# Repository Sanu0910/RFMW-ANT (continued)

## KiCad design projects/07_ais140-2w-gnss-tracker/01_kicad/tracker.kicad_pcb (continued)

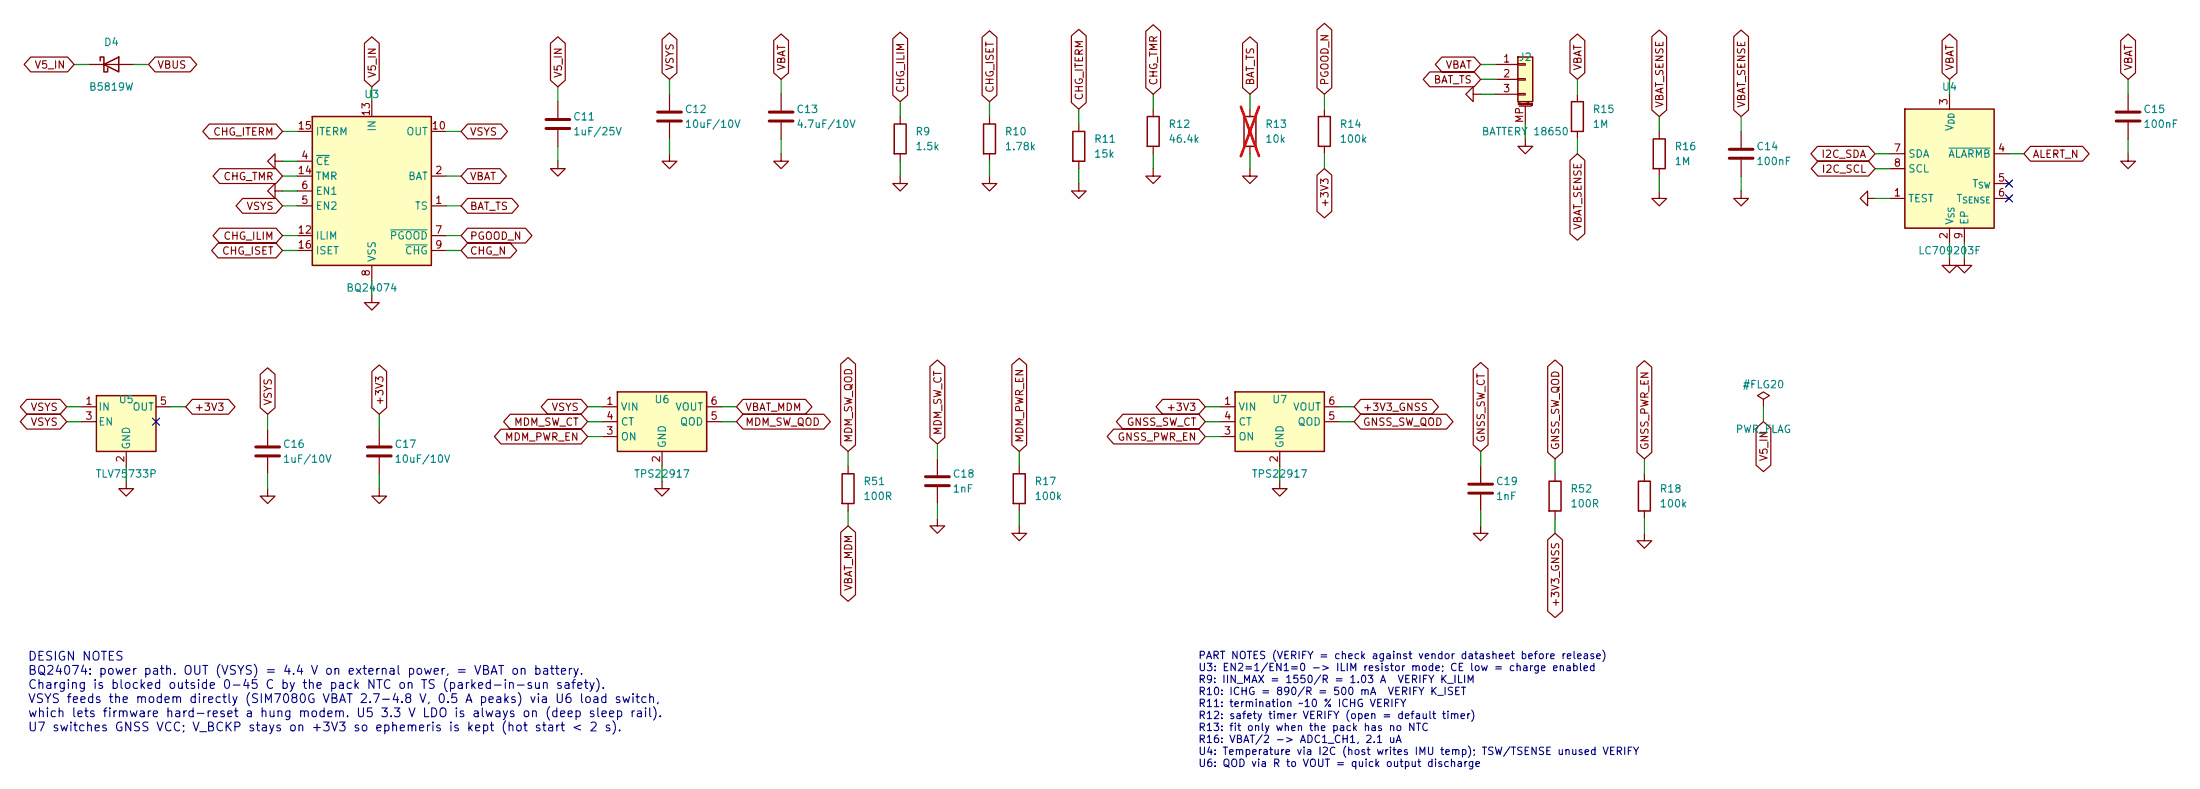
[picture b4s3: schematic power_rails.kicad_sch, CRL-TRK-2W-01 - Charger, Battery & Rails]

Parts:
C11: 1uF/25V; C_0603_1608Metric; MPN 0603 MLCC X7R/X5R, AEC-Q200
C12, C17: 10uF/10V; C_0805_2012Metric; MPN 0805 MLCC X7R/X5R, AEC-Q200
C13: 4.7uF/10V; C_0805_2012Metric; MPN 0805 MLCC X7R/X5R, AEC-Q200
C14, C15: 100nF; C_0402_1005Metric; MPN 0402 MLCC X7R/X5R, AEC-Q200
C16: 1uF/10V; C_0603_1608Metric; MPN 0603 MLCC X7R/X5R, AEC-Q200
C18, C19: 1nF; C_0402_1005Metric; MPN 0402 MLCC X7R/X5R, AEC-Q200
D4: B5819W; D_SOD-123; MPN B5819W
J2: BATTERY 18650; JST_PH_S3B-PH-SM4-TB_1x03-1MP_P2.00mm_Horizontal; MPN S3B-PH-SM4-TB(LF)(SN)
R9: 1.5k; R_0402_1005Metric; MPN 0402 1% thick film, AEC-Q200
R10: 1.78k; R_0402_1005Metric; MPN 0402 1% thick film, AEC-Q200
R11: 15k; R_0402_1005Metric; MPN 0402 1% thick film, AEC-Q200
R12: 46.4k; R_0402_1005Metric; MPN 0402 1% thick film, AEC-Q200
R13: 10k; R_0402_1005Metric; MPN 0402 1% thick film, AEC-Q200; not fitted
R14, R17, R18: 100k; R_0402_1005Metric; MPN 0402 1% thick film, AEC-Q200
R15, R16: 1M; R_0402_1005Metric; MPN 0402 1% thick film, AEC-Q200
R51, R52: 100R; R_0402_1005Metric; MPN 0402 1% thick film, AEC-Q200
U3: BQ24074; VQFN-16-1EP_3x3mm_P0.5mm_EP1.6x1.6mm; MPN BQ24074RGTR
U4: LC709203F; WDFN-8-1EP_4x3mm_P0.65mm_EP2.4x1.8mm; MPN LC709203FQH-01TWG
U5: TLV75733P; SOT-23-5; MPN TLV75733PDBVR
U6, U7: TPS22917; SOT-23-6; MPN TPS22917DBVR

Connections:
+3V3: C17.1, R14.2, U5.5 (OUT), U7.1 (VIN); also elsewhere on the board
+3V3_GNSS: R52.2, U7.6 (VOUT); also elsewhere on the board
ALERT_N: U4.4 (~ALARMB); also elsewhere on the board
BAT_TS: J2.2, R13.1, U3.1 (TS)
CHG_ILIM: R9.1, U3.12 (ILIM)
CHG_ISET: R10.1, U3.16 (ISET)
CHG_ITERM: R11.1, U3.15 (ITERM)
CHG_N: U3.9 (~CHG); also elsewhere on the board
GND: C11.2, C12.2, C13.2, C14.2, C15.2, C16.2, C17.2, C18.2, C19.2, J2.3, J2.MP (MountPin), R9.2, R10.2, R11.2, R12.2, R13.2, R16.2, R17.2, R18.2, U3.4 (~CE), U3.6 (EN1), U3.8 (VSS), U3.17 (VSS), U4.1 (TEST), U4.2 (V_{SS}), U4.9 (EP), U5.2 (GND), U6.2 (GND), U7.2 (GND); also elsewhere on the board
GNSS_PWR_EN: R18.1, U7.3 (ON); also elsewhere on the board
GNSS_SW_CT: C19.1, U7.4 (CT)
GNSS_SW_QOD: R52.1, U7.5 (QOD)
I2C_SCL: U4.8 (SCL); also elsewhere on the board
I2C_SDA: U4.7 (SDA); also elsewhere on the board
MDM_PWR_EN: R17.1, U6.3 (ON); also elsewhere on the board
MDM_SW_CT: C18.1, U6.4 (CT)
MDM_SW_QOD: R51.1, U6.5 (QOD)
unnamed: R12.1, U3.14 (TMR)
PGOOD_N: R14.1, U3.7 (~PGOOD); also elsewhere on the board
V5_IN: C11.1, D4.1 (K), U3.13 (IN); also elsewhere on the board
VBAT: C13.1, C15.1, J2.1, R15.1, U3.2 (BAT), U3.3 (BAT), U4.3 (V_{DD}); also elsewhere on the board
VBAT_MDM: R51.2, U6.6 (VOUT); also elsewhere on the board
VBAT_SENSE: C14.1, R15.2, R16.1; also elsewhere on the board
VBUS: D4.2 (A); also elsewhere on the board
VSYS: C12.1, C16.1, U3.5 (EN2), U3.10 (OUT), U3.11 (OUT), U5.1 (IN), U5.3 (EN), U6.1 (VIN); also elsewhere on the board

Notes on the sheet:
DESIGN NOTES BQ24074: power path. OUT (VSYS) = 4.4 V on external power, = VBAT on battery. Charging is blocked outside 0-45 C by the pack NTC on TS (parked-in-sun safety). VSYS feeds the modem directly (SIM7080G VBAT 2.7-4.8 V, 0.5 A peaks) via U6 load switch, which lets firmware hard-reset a hung 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
PART NOTES (VERIFY = check against vendor datasheet before release) U3: EN2=1/EN1=0 -> ILIM resistor mode; CE low = charge enabled R9: IIN_MAX = 1550/R = 1.03 A VERIFY K_ILIM R10: ICHG = 890/R = 500 mA VERIFY K_ISET R11: termination ~10 % ICHG VERIFY R12: safety timer VERIFY (open = default timer) 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

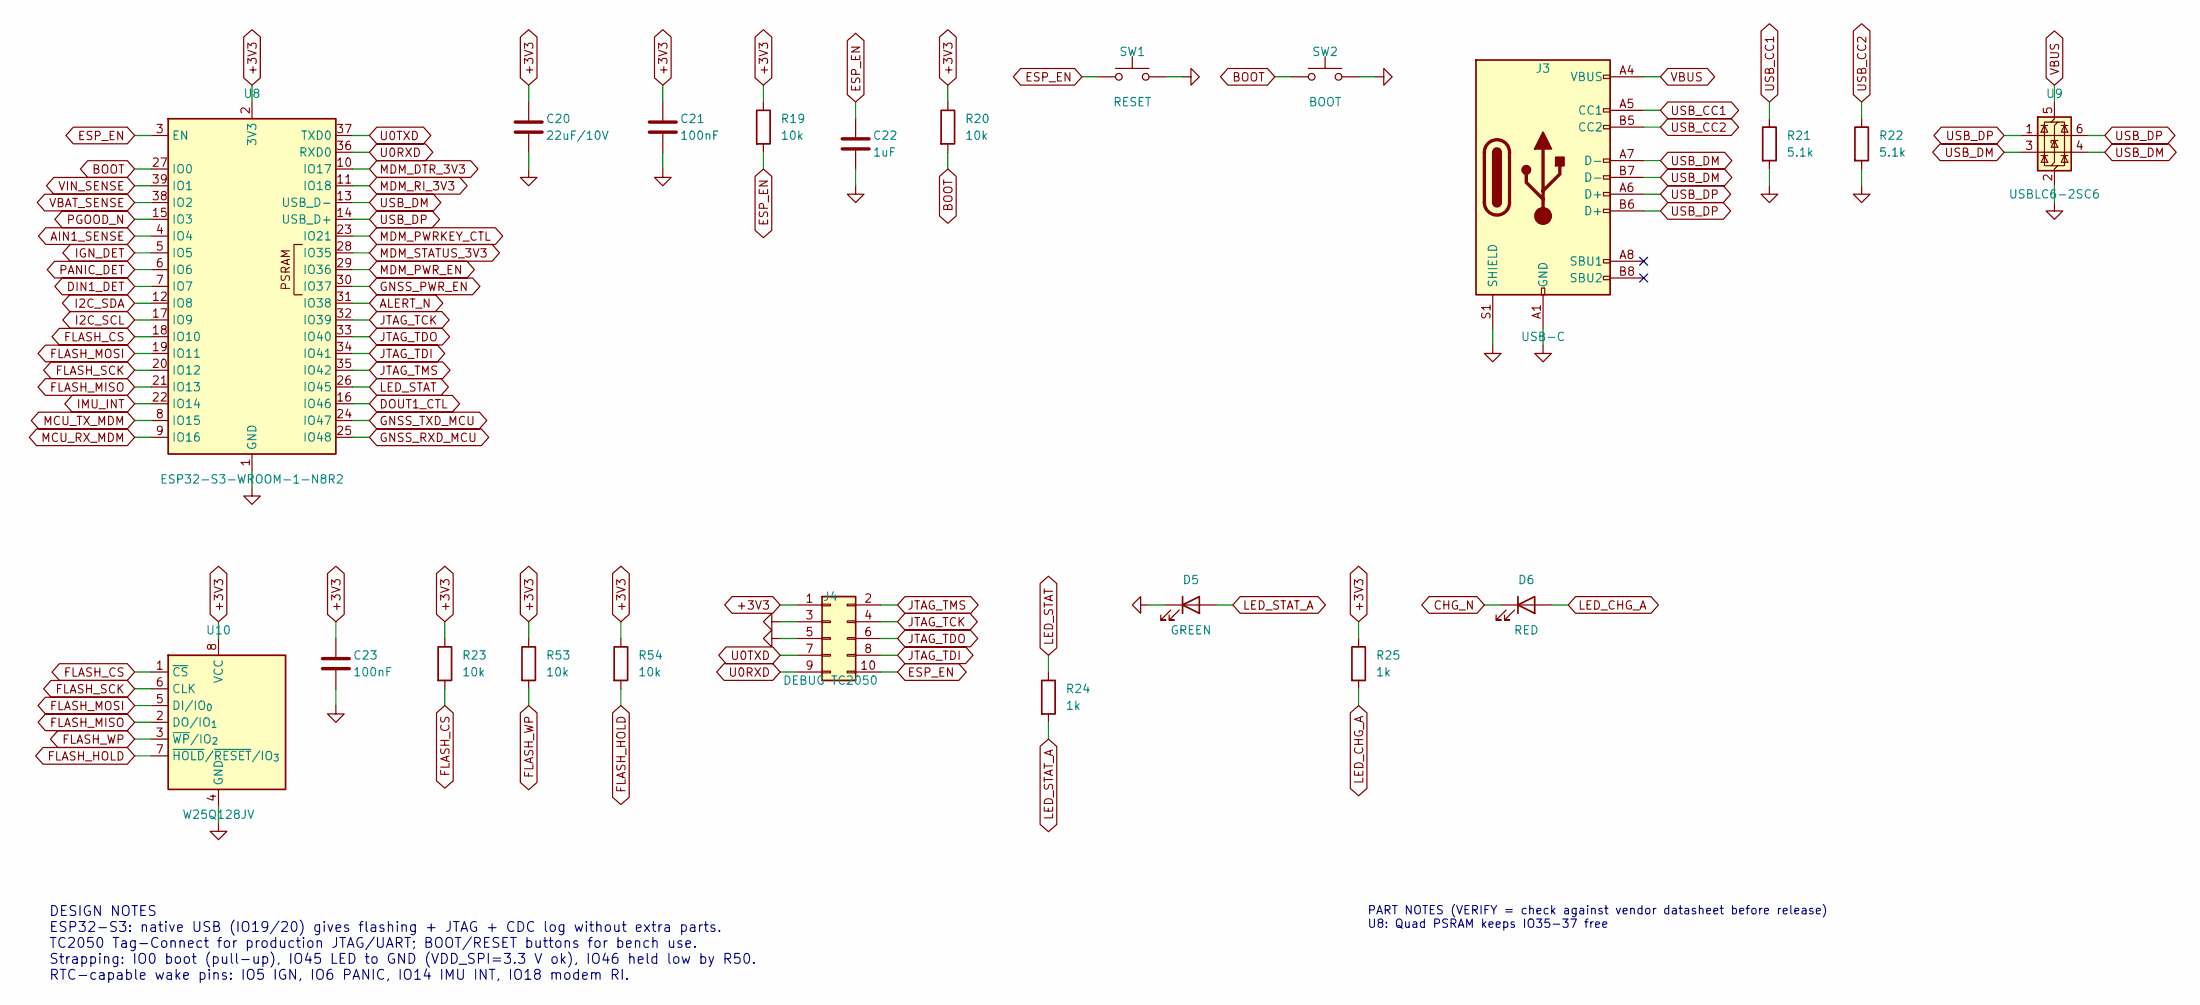
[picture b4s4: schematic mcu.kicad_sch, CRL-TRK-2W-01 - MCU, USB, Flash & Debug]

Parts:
C20: 22uF/10V; C_0805_2012Metric; MPN 0805 MLCC X7R/X5R, AEC-Q200
C21, C23: 100nF; C_0402_1005Metric; MPN 0402 MLCC X7R/X5R, AEC-Q200
C22: 1uF; C_0603_1608Metric; MPN 0603 MLCC X7R/X5R, AEC-Q200
D5: GREEN; LED_0603_1608Metric; MPN LTST-C191KGKT
D6: RED; LED_0603_1608Metric; MPN LTST-C191KRKT
J3: USB-C; USB_C_Receptacle_HRO_TYPE-C-31-M-12; MPN TYPE-C-31-M-12
J4: DEBUG TC2050; Tag-Connect_TC2050-IDC-NL_2x05_P1.27mm_Vertical; MPN Tag-Connect TC2050-IDC-NL (footprint on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
R19, R20, R23, R53, R54: 10k; R_0402_1005Metric; MPN 0402 1% thick film, AEC-Q200
R21, R22: 5.1k; R_0402_1005Metric; MPN 0402 1% thick film, AEC-Q200
R24, R25: 1k; R_0402_1005Metric; MPN 0402 1% thick film, AEC-Q200
SW1: RESET; SW_Push_1P1T_XKB_TS-1187A; MPN TS-1187A-B-A-B
SW2: BOOT; SW_Push_1P1T_XKB_TS-1187A; MPN TS-1187A-B-A-B
U8: ESP32-S3-WROOM-1-N8R2; ESP32-S3-WROOM-1_EdgeAntenna; MPN ESP32-S3-WROOM-1-N8R2
U9: USBLC6-2SC6; SOT-23-6; MPN USBLC6-2SC6
U10: W25Q128JV; SOIC-8_5.3x5.3mm_P1.27mm; MPN W25Q128JVSIQ

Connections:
+3V3: C20.1, C21.1, C23.1, J4.1, R19.1, R20.1, R23.1, R25.1, R53.1, R54.1, U8.2 (3V3), U10.8 (VCC); also elsewhere on the board
AIN1_SENSE: U8.4 (IO4); also elsewhere on the board
ALERT_N: U8.31 (IO38); also elsewhere on the board
BOOT: R20.2, SW2.1, U8.27 (IO0); also elsewhere on the board
CHG_N: D6.1 (K); also elsewhere on the board
DIN1_DET: U8.7 (IO7); also elsewhere on the board
DOUT1_CTL: U8.16 (IO46); also elsewhere on the board
ESP_EN: C22.1, J4.10, R19.2, SW1.1, U8.3 (EN); also elsewhere on the board
FLASH_CS: R23.2, U8.18 (IO10), U10.1 (~CS)
FLASH_HOLD: R54.2, U10.7 (~HOLD/~RESET/IO_{3})
FLASH_MISO: U8.21 (IO13), U10.2 (DO/IO_{1})
FLASH_MOSI: U8.19 (IO11), U10.5 (DI/IO_{0})
FLASH_SCK: U8.20 (IO12), U10.6 (CLK)
FLASH_WP: R53.2, U10.3 (~WP/IO_{2})
GND: C20.2, C21.2, C22.2, C23.2, D5.1 (K), J3.A1 (GND), J3.A12 (GND), J3.B1 (GND), J3.B12 (GND), J3.S1 (SHIELD), J4.3, J4.5, R21.2, R22.2, SW1.2, SW2.2, U8.1 (GND), U8.40 (GND), U8.41 (GND), U9.2 (GND), U10.4 (GND); also elsewhere on the board
GNSS_PWR_EN: U8.30 (IO37); also elsewhere on the board
GNSS_RXD_MCU: U8.25 (IO48); also elsewhere on the board
GNSS_TXD_MCU: U8.24 (IO47); also elsewhere on the board
I2C_SCL: U8.17 (IO9); also elsewhere on the board
I2C_SDA: U8.12 (IO8); also elsewhere on the board
IGN_DET: U8.5 (IO5); also elsewhere on the board
IMU_INT: U8.22 (IO14); also elsewhere on the board
JTAG_TCK: J4.4, U8.32 (IO39); also elsewhere on the board
JTAG_TDI: J4.8, U8.34 (IO41); also elsewhere on the board
JTAG_TDO: J4.6, U8.33 (IO40); also elsewhere on the board
JTAG_TMS: J4.2, U8.35 (IO42); also elsewhere on the board
LED_CHG_A: D6.2 (A), R25.2
LED_STAT: R24.1, U8.26 (IO45)
LED_STAT_A: D5.2 (A), R24.2
MCU_RX_MDM: U8.9 (IO16); also elsewhere on the board
MCU_TX_MDM: U8.8 (IO15); also elsewhere on the board
MDM_DTR_3V3: U8.10 (IO17); also elsewhere on the board
MDM_PWRKEY_CTL: U8.23 (IO21); also elsewhere on the board
MDM_PWR_EN: U8.29 (IO36); also elsewhere on the board
MDM_RI_3V3: U8.11 (IO18); also elsewhere on the board
MDM_STATUS_3V3: U8.28 (IO35); also elsewhere on the board
PANIC_DET: U8.6 (IO6); also elsewhere on the board
PGOOD_N: U8.15 (IO3); also elsewhere on the board
U0RXD: J4.9, U8.36 (RXD0); also elsewhere on the board
U0TXD: J4.7, U8.37 (TXD0); also elsewhere on the board
USB_CC1: J3.A5 (CC1), R21.1
USB_CC2: J3.B5 (CC2), R22.1
USB_DM: J3.A7 (D-), J3.B7 (D-), U8.13 (USB_D-), U9.3 (I/O2), U9.4 (I/O2)
USB_DP: J3.A6 (D+), J3.B6 (D+), U8.14 (USB_D+), U9.1 (I/O1), U9.6 (I/O1)
VBAT_SENSE: U8.38 (IO2); also elsewhere on the board
VBUS: J3.A4 (VBUS), J3.A9 (VBUS), J3.B4 (VBUS), J3.B9 (VBUS), U9.5 (VBUS); also elsewhere on the board
VIN_SENSE: U8.39 (IO1); also elsewhere on the board

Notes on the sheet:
DESIGN NOTES ESP32-S3: native USB (IO19/20) gives flashing + JTAG + CDC log without extra parts. TC2050 Tag-Connect for production JTAG/UART; BOOT/RESET buttons for bench use. Strapping: IO0 boot (pull-up), IO45 LED to GND (VDD_SPI=3.3 V ok), IO46 held low by R50. RTC-capable wake pins: IO5 IGN, IO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
PART NOTES (VERIFY = check against vendor datasheet before release) U8: Quad PSRAM keeps IO35-37 free

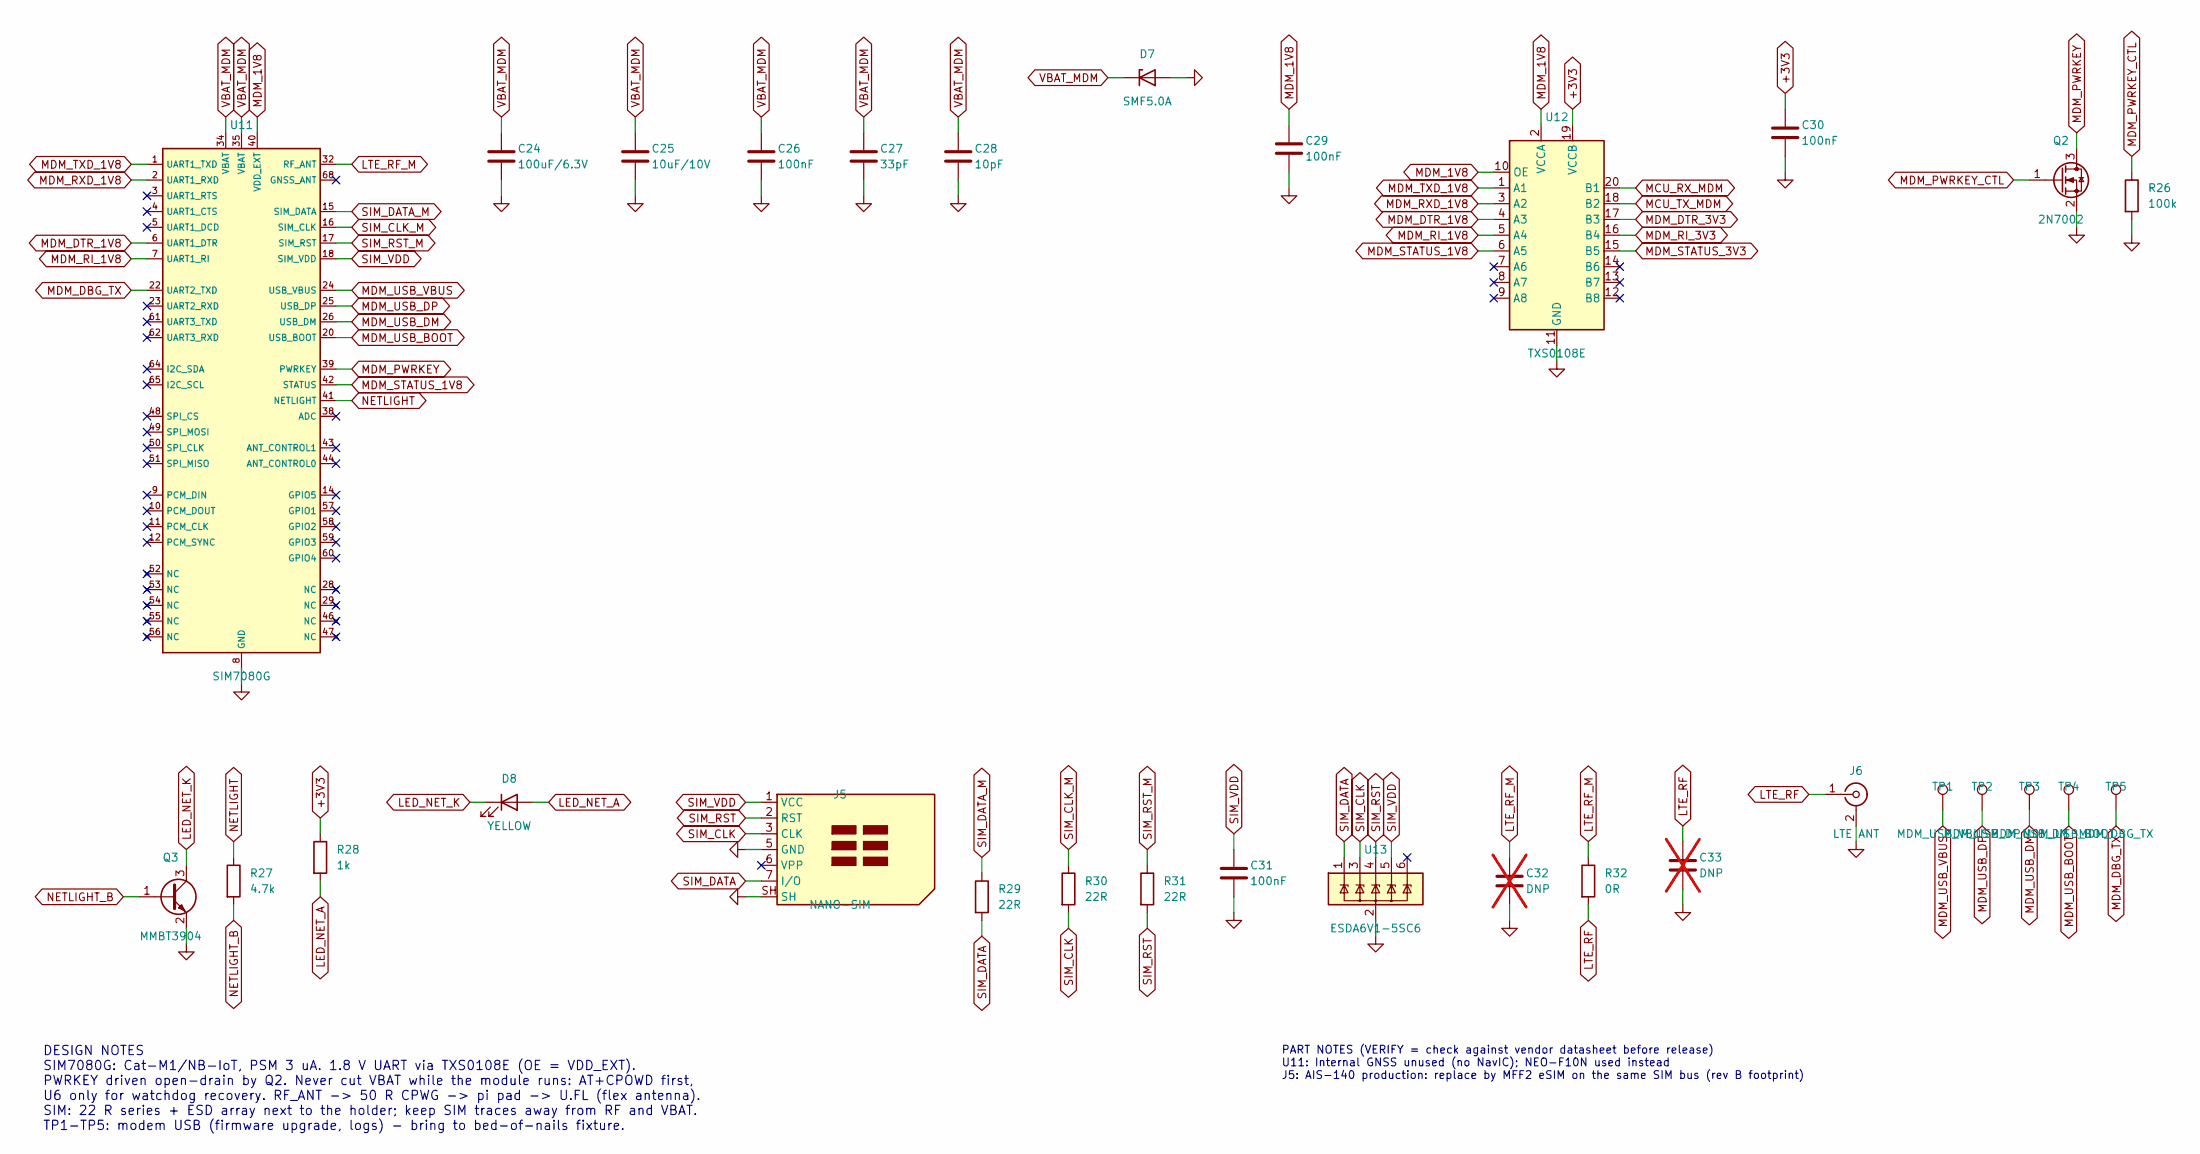
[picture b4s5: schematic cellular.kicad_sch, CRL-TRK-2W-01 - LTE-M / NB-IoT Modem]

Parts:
C24: 100uF/6.3V; C_1210_3225Metric; MPN 1210 MLCC X7R/X5R, AEC-Q200
C25: 10uF/10V; C_0805_2012Metric; MPN 0805 MLCC X7R/X5R, AEC-Q200
C26, C29, C30, C31: 100nF; C_0402_1005Metric; MPN 0402 MLCC X7R/X5R, AEC-Q200
C27: 33pF; C_0402_1005Metric; MPN 0402 C0G 50V
C28: 10pF; C_0402_1005Metric; MPN 0402 C0G 50V
C32, C33: DNP; C_0402_1005Metric; MPN 0402 C0G (tune); not fitted
D7: SMF5.0A; D_SOD-123F; MPN SMF5.0A
D8: YELLOW; LED_0603_1608Metric; MPN LTST-C191KSKT
J5: NANO-SIM; nanoSIM_GCT_SIM8060-6-0-14-00; MPN SIM8060-6-0-14-00-A
J6: LTE ANT; U.FL_Hirose_U.FL-R-SMT-1_Vertical; MPN U.FL-R-SMT-1(10)
Q2: 2N7002; SOT-23; MPN 2N7002K-7
Q3: MMBT3904; SOT-23; MPN MMBT3904
R26: 100k; R_0402_1005Metric; MPN 0402 1% thick film, AEC-Q200
R27: 4.7k; R_0402_1005Metric; MPN 0402 1% thick film, AEC-Q200
R28: 1k; R_0402_1005Metric; MPN 0402 1% thick film, AEC-Q200
R29, R30, R31: 22R; R_0402_1005Metric; MPN 0402 1% thick film, AEC-Q200
R32: 0R; R_0402_1005Metric; MPN 0402 0R jumper
TP1: MDM_USB_VBUS; TestPoint_Pad_D1.0mm; MPN Test pad 1.0 mm (no part)
TP2: MDM_USB_DP; TestPoint_Pad_D1.0mm; MPN Test pad 1.0 mm (no part)
TP3: MDM_USB_DM; TestPoint_Pad_D1.0mm; MPN Test pad 1.0 mm (no part)
TP4: MDM_USB_BOOT; TestPoint_Pad_D1.0mm; MPN Test pad 1.0 mm (no part)
TP5: MDM_DBG_TX; TestPoint_Pad_D1.0mm; MPN Test pad 1.0 mm (no part)
U11: SIM7080G; SIMCom_SIM7080G_LCC-77; MPN SIM7080G
U12: TXS0108E; TSSOP-20_4.4x6.5mm_P0.65mm; MPN TXS0108EPWR
U13: ESDA6V1-5SC6; SOT-23-6; MPN ESDA6V1-5SC6

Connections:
+3V3: C30.1, R28.1, U12.19 (VCCB); also elsewhere on the board
GND: C24.2, C25.2, C26.2, C27.2, C28.2, C29.2, C30.2, C31.2, C32.2, C33.2, D7.2 (A), J5.5 (GND), J5.SH, J6.2 (Ext), Q2.2 (S), Q3.2 (E), R26.2, U11.8 (GND), U11.13 (GND), U11.19 (GND), U11.21 (GND), U11.27 (GND), U11.30 (GND), U11.31 (GND), U11.33 (GND), U11.36 (GND), U11.37 (GND), U11.45 (GND), U11.63 (GND), U11.66 (GND), U11.67 (GND), U11.69 (GND), U11.70 (GND), U11.71 (GND), U11.72 (GND), U11.73 (GND), U11.74 (GND), U11.75 (GND), U11.76 (GND), U11.77 (GND), U12.11 (GND), U13.2 (GND); also elsewhere on the board
LED_NET_A: D8.2 (A), R28.2
LED_NET_K: D8.1 (K), Q3.3 (C)
LTE_RF: C33.1, J6.1 (In), R32.2
LTE_RF_M: C32.1, R32.1, U11.32 (RF_ANT)
MCU_RX_MDM: U12.20 (B1); also elsewhere on the board
MCU_TX_MDM: U12.18 (B2); also elsewhere on the board
MDM_1V8: C29.1, U11.40 (VDD_EXT), U12.2 (VCCA), U12.10 (OE)
MDM_DBG_TX: TP5.1, U11.22 (UART2_TXD)
MDM_DTR_1V8: U11.6 (UART1_DTR), U12.4 (A3)
MDM_DTR_3V3: U12.17 (B3); also elsewhere on the board
MDM_PWRKEY: Q2.3 (D), U11.39 (PWRKEY)
MDM_PWRKEY_CTL: Q2.1 (G), R26.1; also elsewhere on the board
MDM_RI_1V8: U11.7 (UART1_RI), U12.5 (A4)
MDM_RI_3V3: U12.16 (B4); also elsewhere on the board
MDM_RXD_1V8: U11.2 (UART1_RXD), U12.3 (A2)
MDM_STATUS_1V8: U11.42 (STATUS), U12.6 (A5)
MDM_STATUS_3V3: U12.15 (B5); also elsewhere on the board
MDM_TXD_1V8: U11.1 (UART1_TXD), U12.1 (A1)
MDM_USB_BOOT: TP4.1, U11.20 (USB_BOOT)
MDM_USB_DM: TP3.1, U11.26 (USB_DM)
MDM_USB_DP: TP2.1, U11.25 (USB_DP)
MDM_USB_VBUS: TP1.1, U11.24 (USB_VBUS)
NETLIGHT: R27.1, U11.41 (NETLIGHT)
NETLIGHT_B: Q3.1 (B), R27.2
SIM_CLK: J5.3 (CLK), R30.2, U13.3 (IO2)
SIM_CLK_M: R30.1, U11.16 (SIM_CLK)
SIM_DATA: J5.7 (I/O), R29.2, U13.1 (IO1)
SIM_DATA_M: R29.1, U11.15 (SIM_DATA)
SIM_RST: J5.2 (RST), R31.2, U13.4 (IO3)
SIM_RST_M: R31.1, U11.17 (SIM_RST)
SIM_VDD: C31.1, J5.1 (VCC), U11.18 (SIM_VDD), U13.5 (IO4)
VBAT_MDM: C24.1, C25.1, C26.1, C27.1, C28.1, D7.1 (K), U11.34 (VBAT), U11.35 (VBAT); also elsewhere on the board

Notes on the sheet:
DESIGN NOTES SIM7080G: Cat-M1/NB-IoT, PSM 3 uA. 1.8 V UART via TXS0108E (OE = VDD_EXT). PWRKEY driven open-drain by Q2. Never cut VBAT while the module runs: AT+CPOWD first, U6 only for watchdog recovery. RF_ANT -> 50 R CPWG -> pi pad -> U.FL (flex antenna). SIM: 22 R series + ESD array next to the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
PART NOTES (VERIFY = check against vendor datasheet before release) U11: Internal GNSS unused (no NavIC); NEO-F10N used instead J5: AIS-140 production: replace by MFF2 eSIM on the same SIM bus (rev B footprint)

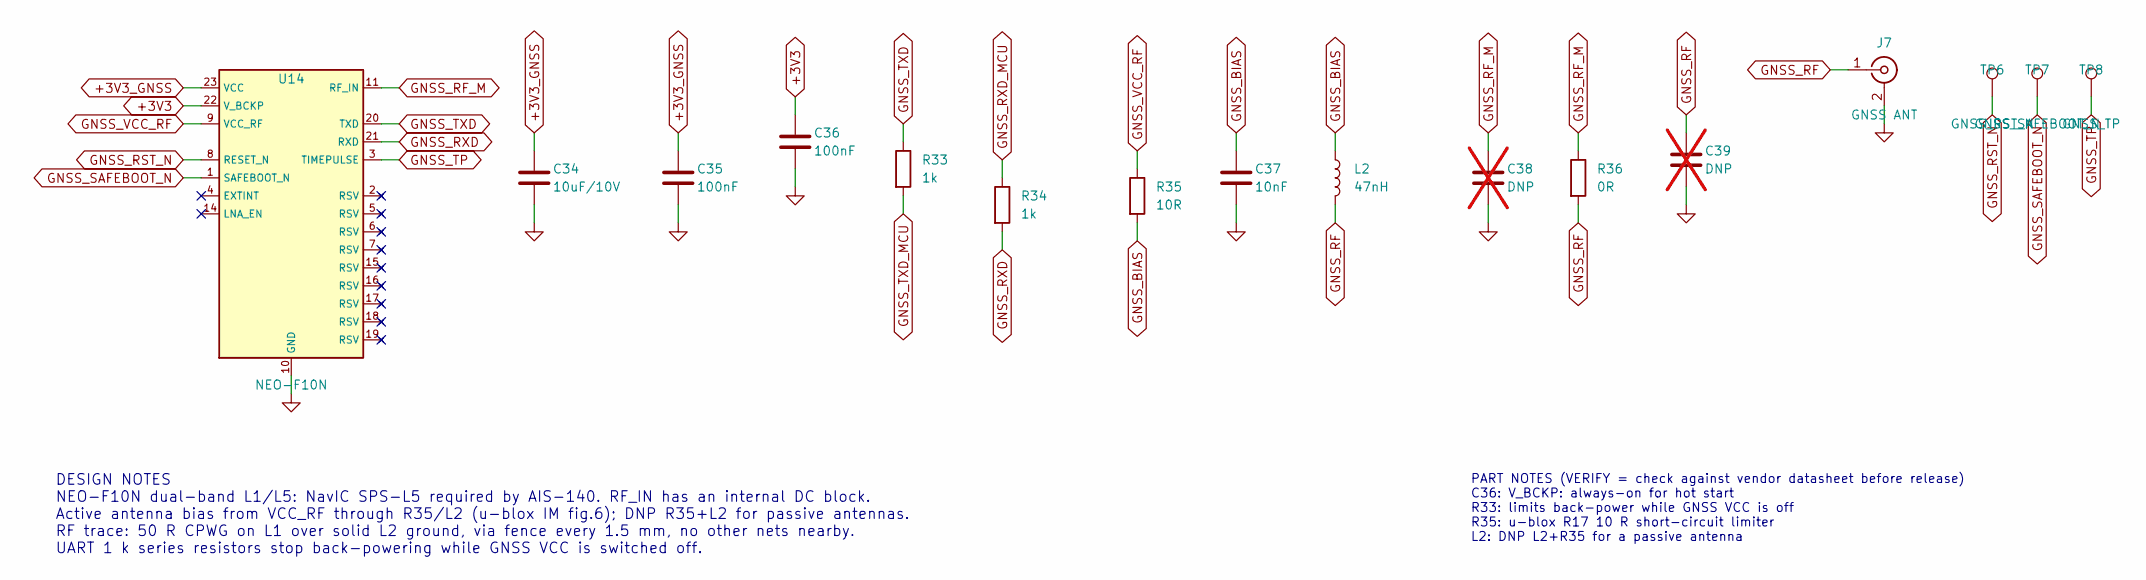
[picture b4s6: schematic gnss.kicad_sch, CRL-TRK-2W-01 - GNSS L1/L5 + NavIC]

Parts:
C34: 10uF/10V; C_0805_2012Metric; MPN 0805 MLCC X7R/X5R, AEC-Q200
C35, C36: 100nF; C_0402_1005Metric; MPN 0402 MLCC X7R/X5R, AEC-Q200
C37: 10nF; C_0402_1005Metric; MPN 0402 MLCC X7R/X5R, AEC-Q200
C38, C39: DNP; C_0402_1005Metric; MPN 0402 C0G (tune); not fitted
J7: GNSS ANT; U.FL_Hirose_U.FL-R-SMT-1_Vertical; MPN U.FL-R-SMT-1(10)
L2: 47nH; L_0402_1005Metric; MPN LQG15HS47NJ02D
R33, R34: 1k; R_0402_1005Metric; MPN 0402 1% thick film, AEC-Q200
R35: 10R; R_0402_1005Metric; MPN 0402 1% thick film, AEC-Q200
R36: 0R; R_0402_1005Metric; MPN 0402 0R jumper
TP6: GNSS_RST_N; TestPoint_Pad_D1.0mm; MPN Test pad 1.0 mm (no part)
TP7: GNSS_SAFEBOOT_N; TestPoint_Pad_D1.0mm; MPN Test pad 1.0 mm (no part)
TP8: GNSS_TP; TestPoint_Pad_D1.0mm; MPN Test pad 1.0 mm (no part)
U14: NEO-F10N; ublox_NEO; MPN NEO-F10N-00B

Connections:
+3V3: C36.1, U14.22 (V_BCKP); also elsewhere on the board
+3V3_GNSS: C34.1, C35.1, U14.23 (VCC); also elsewhere on the board
GND: C34.2, C35.2, C36.2, C37.2, C38.2, C39.2, J7.2 (Ext), U14.10 (GND), U14.12 (GND), U14.13 (GND), U14.24 (GND); also elsewhere on the board
GNSS_BIAS: C37.1, L2.1, R35.2
GNSS_RF: C39.1, J7.1 (In), L2.2, R36.2
GNSS_RF_M: C38.1, R36.1, U14.11 (RF_IN)
GNSS_RST_N: TP6.1, U14.8 (RESET_N)
GNSS_RXD: R34.2, U14.21 (RXD)
GNSS_RXD_MCU: R34.1; also elsewhere on the board
GNSS_SAFEBOOT_N: TP7.1, U14.1 (SAFEBOOT_N)
GNSS_TP: TP8.1, U14.3 (TIMEPULSE)
GNSS_TXD: R33.1, U14.20 (TXD)
GNSS_TXD_MCU: R33.2; also elsewhere on the board
GNSS_VCC_RF: R35.1, U14.9 (VCC_RF)

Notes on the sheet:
DESIGN NOTES NEO-F10N dual-band L1/L5: NavIC SPS-L5 required by AIS-140. RF_IN has an internal DC block. Active antenna bias from VCC_RF through R35/L2 (u-blox IM fig.6); DNP R35+L2 for passive antennas. RF trace: 50 R CPWG on L1 over solid L2 ground, via fence every 1.5 mm, no other nets nearby. U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
PART NOTES (VERIFY = check against vendor datasheet before release) C36: V_BCKP: always-on for hot start R33: limits back-power while GNSS VCC is off R35: u-blox R17 10 R short-circuit limiter L2: DNP L2+R35 for a passive antenna

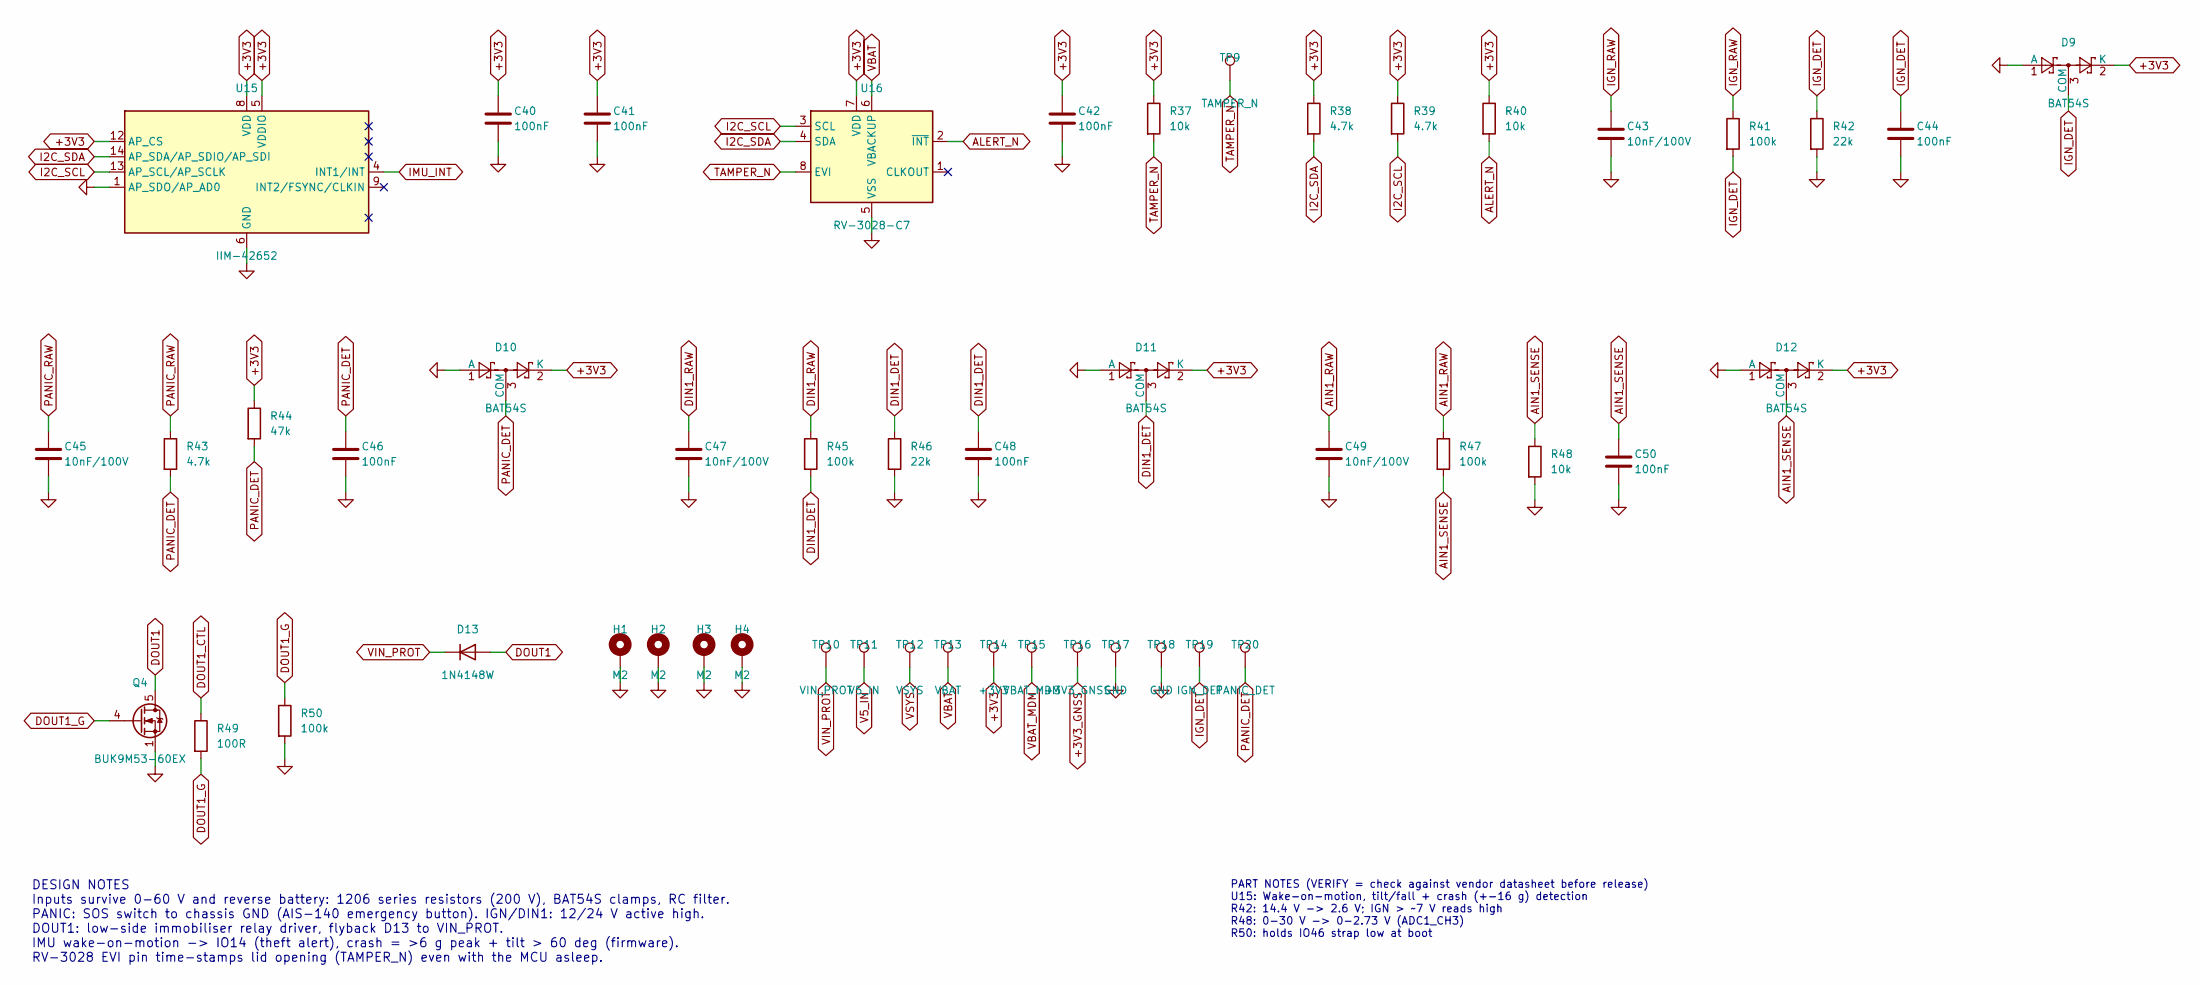
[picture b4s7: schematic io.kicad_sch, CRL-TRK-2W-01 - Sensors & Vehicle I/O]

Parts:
C40, C41, C42, C44, C46, C48, C50: 100nF; C_0402_1005Metric; MPN 0402 MLCC X7R/X5R, AEC-Q200
C43, C45, C47, C49: 10nF/100V; C_0603_1608Metric; MPN 0603 MLCC X7R/X5R, AEC-Q200
D9, D10, D11, D12: BAT54S; SOT-23; MPN BAT54S
D13: 1N4148W; D_SOD-123; MPN 1N4148W-7-F
H1, H2, H3, H4: M2; MountingHole_2.2mm_M2_Pad_Via; MPN M2 self-tapping screw (enclosure boss)
Q4: BUK9M53-60EX; LFPAK33; MPN BUK9M53-60EX
R37, R40, R48: 10k; R_0402_1005Metric; MPN 0402 1% thick film, AEC-Q200
R38, R39: 4.7k; R_0402_1005Metric; MPN 0402 1% thick film, AEC-Q200
R41, R45, R47: 100k; R_1206_3216Metric; MPN 1206 1% thick film, AEC-Q200
R42, R46: 22k; R_0402_1005Metric; MPN 0402 1% thick film, AEC-Q200
R43: 4.7k; R_1206_3216Metric; MPN 1206 1% thick film, AEC-Q200
R44: 47k; R_0402_1005Metric; MPN 0402 1% thick film, AEC-Q200
R49: 100R; R_0402_1005Metric; MPN 0402 1% thick film, AEC-Q200
R50: 100k; R_0402_1005Metric; MPN 0402 1% thick film, AEC-Q200
TP9: TAMPER_N; TestPoint_Pad_D1.0mm; MPN Test pad 1.0 mm (no part)
TP10: VIN_PROT; TestPoint_Pad_D1.0mm; MPN Test pad 1.0 mm (no part)
TP11: V5_IN; TestPoint_Pad_D1.0mm; MPN Test pad 1.0 mm (no part)
TP12: VSYS; TestPoint_Pad_D1.0mm; MPN Test pad 1.0 mm (no part)
TP13: VBAT; TestPoint_Pad_D1.0mm; MPN Test pad 1.0 mm (no part)
TP14: +3V3; TestPoint_Pad_D1.0mm; MPN Test pad 1.0 mm (no part)
TP15: VBAT_MDM; TestPoint_Pad_D1.0mm; MPN Test pad 1.0 mm (no part)
TP16: +3V3_GNSS; TestPoint_Pad_D1.0mm; MPN Test pad 1.0 mm (no part)
TP17, TP18: GND; TestPoint_Pad_D1.0mm; MPN Test pad 1.0 mm (no part)
TP19: IGN_DET; TestPoint_Pad_D1.0mm; MPN Test pad 1.0 mm (no part)
TP20: PANIC_DET; TestPoint_Pad_D1.0mm; MPN Test pad 1.0 mm (no part)
U15: IIM-42652; Bosch_LGA-14_3x2.5mm_P0.5mm; MPN IIM-42652
U16: RV-3028-C7; MicroCrystal_C7_SON-8_1.5x3.2mm_P0.9mm; MPN RV-3028-C7 32.768kHz 1ppm-TA-QC

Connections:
+3V3: C40.1, C41.1, C42.1, D9.2 (K), D10.2 (K), D11.2 (K), D12.2 (K), R37.1, R38.1, R39.1, R40.1, R44.1, TP14.1, U15.5 (VDDIO), U15.8 (VDD), U15.12 (AP_CS), U16.7 (VDD); also elsewhere on the board
+3V3_GNSS: TP16.1; also elsewhere on the board
AIN1_RAW: C49.1, R47.1; also elsewhere on the board
AIN1_SENSE: C50.1, D12.3 (COM), R47.2, R48.1; also elsewhere on the board
ALERT_N: R40.2, U16.2 (~INT); also elsewhere on the board
DIN1_DET: C48.1, D11.3 (COM), R45.2, R46.1; also elsewhere on the board
DIN1_RAW: C47.1, R45.1; also elsewhere on the board
DOUT1: D13.2 (A), Q4.5 (D); also elsewhere on the board
DOUT1_CTL: R49.1; also elsewhere on the board
DOUT1_G: Q4.4 (G), R49.2, R50.1
GND: C40.2, C41.2, C42.2, C43.2, C44.2, C45.2, C46.2, C47.2, C48.2, C49.2, C50.2, D9.1 (A), D10.1 (A), D11.1 (A), D12.1 (A), H1.1, H2.1, H3.1, H4.1, Q4.1 (S), Q4.2 (S), Q4.3 (S), R42.2, R46.2, R48.2, R50.2, TP17.1, TP18.1, U15.1 (AP_SDO/AP_AD0), U15.6 (GND), U15.7 (GND), U16.5 (VSS); also elsewhere on the board
I2C_SCL: R39.2, U15.13 (AP_SCL/AP_SCLK), U16.3 (SCL); also elsewhere on the board
I2C_SDA: R38.2, U15.14 (AP_SDA/AP_SDIO/AP_SDI), U16.4 (SDA); also elsewhere on the board
IGN_DET: C44.1, D9.3 (COM), R41.2, R42.1, TP19.1; also elsewhere on the board
IGN_RAW: C43.1, R41.1; also elsewhere on the board
IMU_INT: U15.4 (INT1/INT); also elsewhere on the board
PANIC_DET: C46.1, D10.3 (COM), R43.2, R44.2, TP20.1; also elsewhere on the board
PANIC_RAW: C45.1, R43.1; also elsewhere on the board
TAMPER_N: R37.2, TP9.1, U16.8 (EVI)
V5_IN: TP11.1; also elsewhere on the board
VBAT: TP13.1, U16.6 (VBACKUP); also elsewhere on the board
VBAT_MDM: TP15.1; also elsewhere on the board
VIN_PROT: D13.1 (K), TP10.1; also elsewhere on the board
VSYS: TP12.1; also elsewhere on the board

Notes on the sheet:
DESIGN NOTES Inputs survive 0-60 V and reverse battery: 1206 series resistors (200 V), BAT54S clamps, RC filter. PANIC: SOS switch to chassis GND (AIS-140 emergency button). IGN/DIN1: 12/24 V active high. DOUT1: low-side immobiliser relay driver, flyback D13 to VIN_PROT. IMU wake-on-motion -> IO14 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
PART NOTES (VERIFY = check against vendor datasheet before release) U15: Wake-on-motion, tilt/fall + crash (+-16 g) detection R42: 14.4 V -> 2.6 V; IGN > ~7 V reads high R48: 0-30 V -> 0-2.73 V (ADC1_CH3) R50: holds IO46 strap low at boot
